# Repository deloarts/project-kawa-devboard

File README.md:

# Project Kawa Devboard

Documentation for the **Project Kawa Devboard**. This repository contains everything the Wifi-Client requires, including code, circuit design and housing.

> ⚠️ The Kawa Devboard is part of my condition monitoring project - Project Kawa - which isn't public. However, this repo is public, because the development board itself works pretty well after a long-term test of now over a year. You can use this board for your own project, if it fits your needs.
> 
> ✏️ The board is compatible with most open source home-automation systems, so feel free to use this board for other appliances than the Project Kawa.
>
> ✏️ In this repo you'll find not only the hardware of the devboard, but also the source. Keep in mind that the code is written for the Project Kawa Server, which isn't public, but feel free to tweak it for your own application.

## Table of contents

- [Project Kawa Devboard](#project-kawa-devboard)
  - [Table of contents](#table-of-contents)
  - [1 Description](#1-description)
  - [2 Usage](#2-usage)
    - [2.1 LED indicator](#21-led-indicator)
    - [2.2 Setup wifi](#22-setup-wifi)
    - [2.3 Reading sensor data](#23-reading-sensor-data)
    - [2.4 Status codes](#24-status-codes)
  - [3 Hardware](#3-hardware)
    - [3.1 Board](#31-board)
    - [3.2 Housing](#32-housing)
  - [4 Environment](#4-environment)
    - [4.1 Used software](#41-used-software)
    - [4.2 VS-Code setup](#42-vs-code-setup)
      - [4.2.1 code-workspace](#421-code-workspace)
      - [4.2.2 arduino.json](#422-arduinojson)
      - [4.2.3 c\_cpp\_properties.json](#423-c_cpp_propertiesjson)
    - [4.3 Eagle libraries](#43-eagle-libraries)
  - [5 Building \& Debugging](#5-building--debugging)
    - [5.1 Initial upload](#51-initial-upload)
    - [5.2 OTA upload](#52-ota-upload)
    - [5.3 Build the firmware](#53-build-the-firmware)
    - [5.4 Build the filesystem](#54-build-the-filesystem)
    - [5.5 Debug](#55-debug)
  - [6 License \& Disclaimer](#6-license--disclaimer)
  - [7 Changelog](#7-changelog)
    - [7.1 Firmware](#71-firmware)
    - [7.2 Filesystem](#72-filesystem)
    - [7.3 PCB](#73-pcb)
    - [7.4 Housing](#74-housing)
  - [8 To Do](#8-to-do)

## 1 Description

**Project Kawa Devboard** is part of the **Project Kawa** environment. This client is designed to test new sensors or new firmware, to debug code or find optimizations in the PCB layout. The latest version may not work without properly -> nightly builds.

This repository contains mostly code that is in development, as well as hardware-design that might only work under special conditions or differ from this documentation. This is not an out-of-the-box solution and requires some knowledge in a variety of fields. If you don't have an education in the field of electronics you should not proceed with this project, you might harm yourself or create damage by the risk of fire. Further you should be comfortable working with VS Code Workspaces.

Please note: All paths and settings are described for Windows. Will be updated in the future.

## 2 Usage

**This requires a working build of the firmware and filesystem already flashed to the chip, see [Initial Upload](#51-initial-upload)**. Please note: The description can differ from the actual process, depending on the development state of this device.

### 2.1 LED indicator

There are different kinds of LED-states to indicate the device's status:

- Short, almost unnoticeable blink: Wakeup from deepsleep, running normal cycle
- Rapid blinking 25 times: Wifi is not setup (this should happen after the initial upload)
- Rapid blinking 2 times: Changes have been written to the config
- On-Off every one second: Wifi-setup is running, hotspot is open

### 2.2 Setup wifi

The device needs to connect to your local network via 2.4GHz wifi. To setup your network's credentials you need to

- press and hold **BUTTON 1**
- click the **RESET** button
- the device opens a hotspot called **kawa setup**
- connect any wifi-enabled device to it
- enter your network-credentials
- select the connected sensor
- select the sleep interval (shorter intervals should only be used for testing and debugging)
- reset the controller afterwards

Now your *Kawa Devboard* is ready for use. As soon as the device connects to your wifi it will automatically connect to the server by its own, assuming that the server is running.

Note: The captive portal may not work properly, if so try:

- Use another device
- Click **yes** if your device asks you to stay connected (happens when the device notices, that no internet connection is available)
- Refresh the captive portal redirection page (sometimes the script or the stylesheet aren't loaded properly)
- Enter the IP address **1.2.3.4** manually into a browser

### 2.3 Reading sensor data

Once the wifi credentials are set up correct the device starts its main task: reading sensor data. There is no further interaction needed. The data is sent as json, example:

```json
{
  "device": {
    "id": "179309432879183923",
    "boardname": "devboard",
    "firmware_version": "0.1.0",
    "filesystem_version": "0.1.0",
    "mode": "production",
    "sensor_status": true,
    "sensor_name": "BMP280",
    "battery_status": true,
    "battery_value": 3.30,
    "sleep_interval": 3600,
    "connection_time": 7.334,
    "ssid": "the_network_ssid",
    "dbm": -78,
    "quality": 44,
    "hostname": "kawa_179309432879183923",
    "ip_address": "192.168.0.200",
    "mac_address": "00:80:41:ae:fd:7e"
  },
  "data": {
    "temperature": {
      "value": 25.2,
      "unit": "°C"
    },
    "pressure": {
      "value": 989.2,
      "unit": "mBar"
    },
    "altitude": {
      "value": 433,
      "unit": "m"
    },
    "humidity": {
      "value": 44.23,
      "unit": "%"
    }
  }
}
```

The server must answer with status code 201 and a json of the following format:

```json
value = {
    "status": "ok",
    "update_firmware": false,
    "new_firmware": "0.0.0",
    "update_spiffs": false,
    "new_spiffs": "0.0.0"
}
```

Due to the OTA-update functionality the client must know when to update. This is done by toggling the respective keys to **true**. With this the client will instantly download the given new version. The maximum size of the json is 2048 bytes.

### 2.4 Status codes

The devices accepts the following status codes as answer when posting data:

- **201**: data has been added to the database
- **406**: data has not been added to the database
- **500**: server error

## 3 Hardware

The core of this application is a ESP12F SOC by [espressif](https://www.espressif.com/en/products/socs/esp8266).

### 3.1 Board

The board is a two layered pcb, with mostly push-through components. This is due to easier hacking into the system, when something new needs testing without making a new pcb.

A complete bill of material can be found inside the [bom folder](docs/bom/).
For the production files select the latest zip-file inside the boards folder.

**Important note**: There is no deep discharge protection for the battery. Do not use non-protected batteries with this setup!

### 3.2 Housing

The housing is made with a 3D printer, files can be found inside the projects cad folder. More information will be added.

## 4 Environment

### 4.1 Used software

- The firmware is created with [VS Code](https://code.visualstudio.com/download) with the [Arduino-Core](https://www.arduino.cc/en/software) (extension: CTRL+P -> *ext install vscode-arduino*))
- The content of the filesystem is compiled with [mkspiffs](https://github.com/igrr/mkspiffs) and uploaded with [esptool](https://github.com/espressif/esptool).
- The pcb design is done with [Autodesk Eagle 9.6.2](https://www.autodesk.de/products/eagle/free-download), but may be continued with [EasyEDA](https://easyeda.com/) due to a better library-to-production support.

A full list of the used software, including versions, libraries and tools can be found at the top of the [src.ino](code/src/src.ino).

### 4.2 VS-Code setup

#### 4.2.1 code-workspace

Workspace-root is the repository-root. All relative paths are from this directory. Add the repository-root to a new workspace and save this workspace (can be saved inside or outside of the repo).

#### 4.2.2 arduino.json

Stored inside the **.vscode/** folder. This folder does not exist when cloning the repo and should appear automatically after creating the workspace, if not:

- Create it: [command-palette](https://code.visualstudio.com/docs/getstarted/userinterface#_command-palette) -> *Arduino: Initialize*
- Edit it: [command-palette](https://code.visualstudio.com/docs/getstarted/userinterface#_command-palette) -> *Arduino: Board Config*

Take the current board config from the description at the top of the [src file](code/src/src.ino).

Add the following lines to the json-file:

```json
  "sketch": "code\\src\\src.ino",
  "output": "code\\build\\firmware\\latest",
```

For the Arduino-Board-Config see the header-comment of the src-file.

#### 4.2.3 c_cpp_properties.json

Stored inside the **.vscode/** folder, create (or add):

```json
"configurations": [
    {
        "name": "Win32",
        "intelliSenseMode": "gcc-x64",
        "includePath": [
            "${workspaceRoot}\\code\\src\\",
            "${workspaceRoot}\\code\\src\\headers\\**",
            "C:\\Program Files (x86)\\Arduino\\hardware\\arduino\\avr\\cores\\arduino\\**",
            "${env:LOCALAPPDATA}\\Arduino15\\packages\\esp8266\\tools\\**",
            "${env:LOCALAPPDATA}\\Arduino15\\packages\\esp8266\\hardware\\esp8266\\3.0.0\\**",
            "${env:LOCALAPPDATA}\\Arduino15\\packages\\esp8266\\hardware\\esp8266\\3.0.0\\libraries\\**",
            "${env:HOMEPATH}\\Documents\\Arduino\\libraries\\ArduinoJson\\**",
            "${env:HOMEPATH}\\Documents\\Arduino\\libraries\\DallasTemperature\\**",
            "${env:HOMEPATH}\\Documents\\Arduino\\libraries\\OneWire\\**",
            "${env:HOMEPATH}\\Documents\\Arduino\\libraries\\Adafruit_Unified_Sensor\\**",
            "${workspaceRoot}\\code\\assets\\libraries\\Adafruit_BME280_Library\\**"
        ],
        "forcedInclude": [
            "C:\\Program Files (x86)\\Arduino\\hardware\\arduino\\avr\\cores\\arduino\\Arduino.h"
        ],
        "cStandard": "c11",
        "cppStandard": "c++17",
        "defines": []
    }
]
```

Please note: Some include-paths are only valid if you have chosen the standard path when you installed the Arduino-IDE on a Windows computer.

### 4.3 Eagle libraries

Can be found inside the pcb-folder. Must not be added to EAGLE if you don't plan on changing the board.

## 5 Building & Debugging

Tested and released firmware and filesystem versions can be found inside the respective folder

- [Firmware](code/build/firmware/)
- [Filesystem](code/build/filesystem/)

Those firmware-versions with the letter **d** after the version indicator are debug-versions. This means that you can hookup a serial-to-usb chip and get debug messages printed to a serial monitor. Baud-rate is always 115200. Versions without that letter are for production environment, you won't get any messages printed to the serial port.

### 5.1 Initial upload

To flash the firmware and filesystem initially you need to upload both with a usb-to-serial converter (popular method: use a [FTDI232 module](https://ftdichip.com/drivers/)). The upload process requires you to

- press and hold the **UPLOAD** button
- press and release the **RESET** button
- release the **UPLOAD** button as soon as the upload begins
- click the **RESET** button after the upload is done

The initial firmware can be uploaded with the command-palette -> *Arduino: Upload*.

The initial filesystem can be uploaded with *[SPIFFS for Arduino](https://github.com/esp8266/arduino-esp8266fs-plugin/releases)*.

### 5.2 OTA upload

New firmware/filesystem will be automatically installed by the **Project Kawa Server**. With every post-request (device -> server) the server answers with the newest firmware/filesystem version. If the current one is older the device will download and install the latest one. This process is called OTA.

This requires a working initial firmware to be flashed onto the device, see [Initial Setup](#51-initial-upload).

In order for the OTA to work you then have to copy the newest firmware/filesystem into the server's bin-directory. Please refer to the server's documentation for the correct filename or use the [test server](code/dev/test_server/test_server.py) from the **/dev** folder. The test server returns only the file set at the top-section. Do not use the test server in a production environment.

### 5.3 Build the firmware

The firmware is built when the src-file is compiled without any errors (command-palette -> *Arduino: Verify*). The binary file is then stored inside the latest-folder of build-directory, as instructed in the *4.2.2 arduino.json*.

### 5.4 Build the filesystem

Currently in testing.

### 5.5 Debug

To debug the firmware uncomment the **#define DEBUG** statement inside the [definitions.h](code/src/headers/definitions.h) file. Connect a serial-to-usb device to the RX-TX pins of the device, upload the changed code and open the serial monitor with 115200 baud rate.

To debug the captive portal content (files inside the [data folder](code/src/data/)) you can use any static file server. Tip: Run Python's builtin module **python -m http.server** inside the data folder.

## 6 License & Disclaimer

MIT.

All content on this repository is provided **as is**. None of these components have been tested or certified. The use of this content is **at your own risk**.

## 7 Changelog

### 7.1 Firmware

**v0.1.2**: Updated libraries.  
**v0.1.1**: Updated battery range.  
**v0.1.0**: Added location and updated api.  
**v0.0.0**: Creation.

### 7.2 Filesystem

**v0.1.0**: Added location.  
**v0.0.0**: Creation.

### 7.3 PCB

**Rev0**: Creation.

### 7.4 Housing

**Rev1**: Updated for FFF.  
**Rev0**: Creation.

## 8 To Do

- [ ] Fix: Wifi settings are overwritten when filesystem gets updated.
- [ ] Fix: Slow/laggy captive portal.
- [ ] Fix: Replace FS with LittleFS.
- [ ] Fix: Allow only one client at the captive portal.
- [ ] Replace: Change frontend to Vue CLI.
- [ ] Add: Switch sensor.
- [ ] Add: Air quality sensor.
- [ ] Add: Rain sensor (amount and state).
- [ ] Add: Moisture sensor.
- [ ] Add: Analog input (may require additional hardware).
- [ ] Test: Relay output (requires additional hardware).
- [ ] Test: LED controller (requires additional hardware).
- [ ] Test: Deep discharge protection (requires additional hardware).

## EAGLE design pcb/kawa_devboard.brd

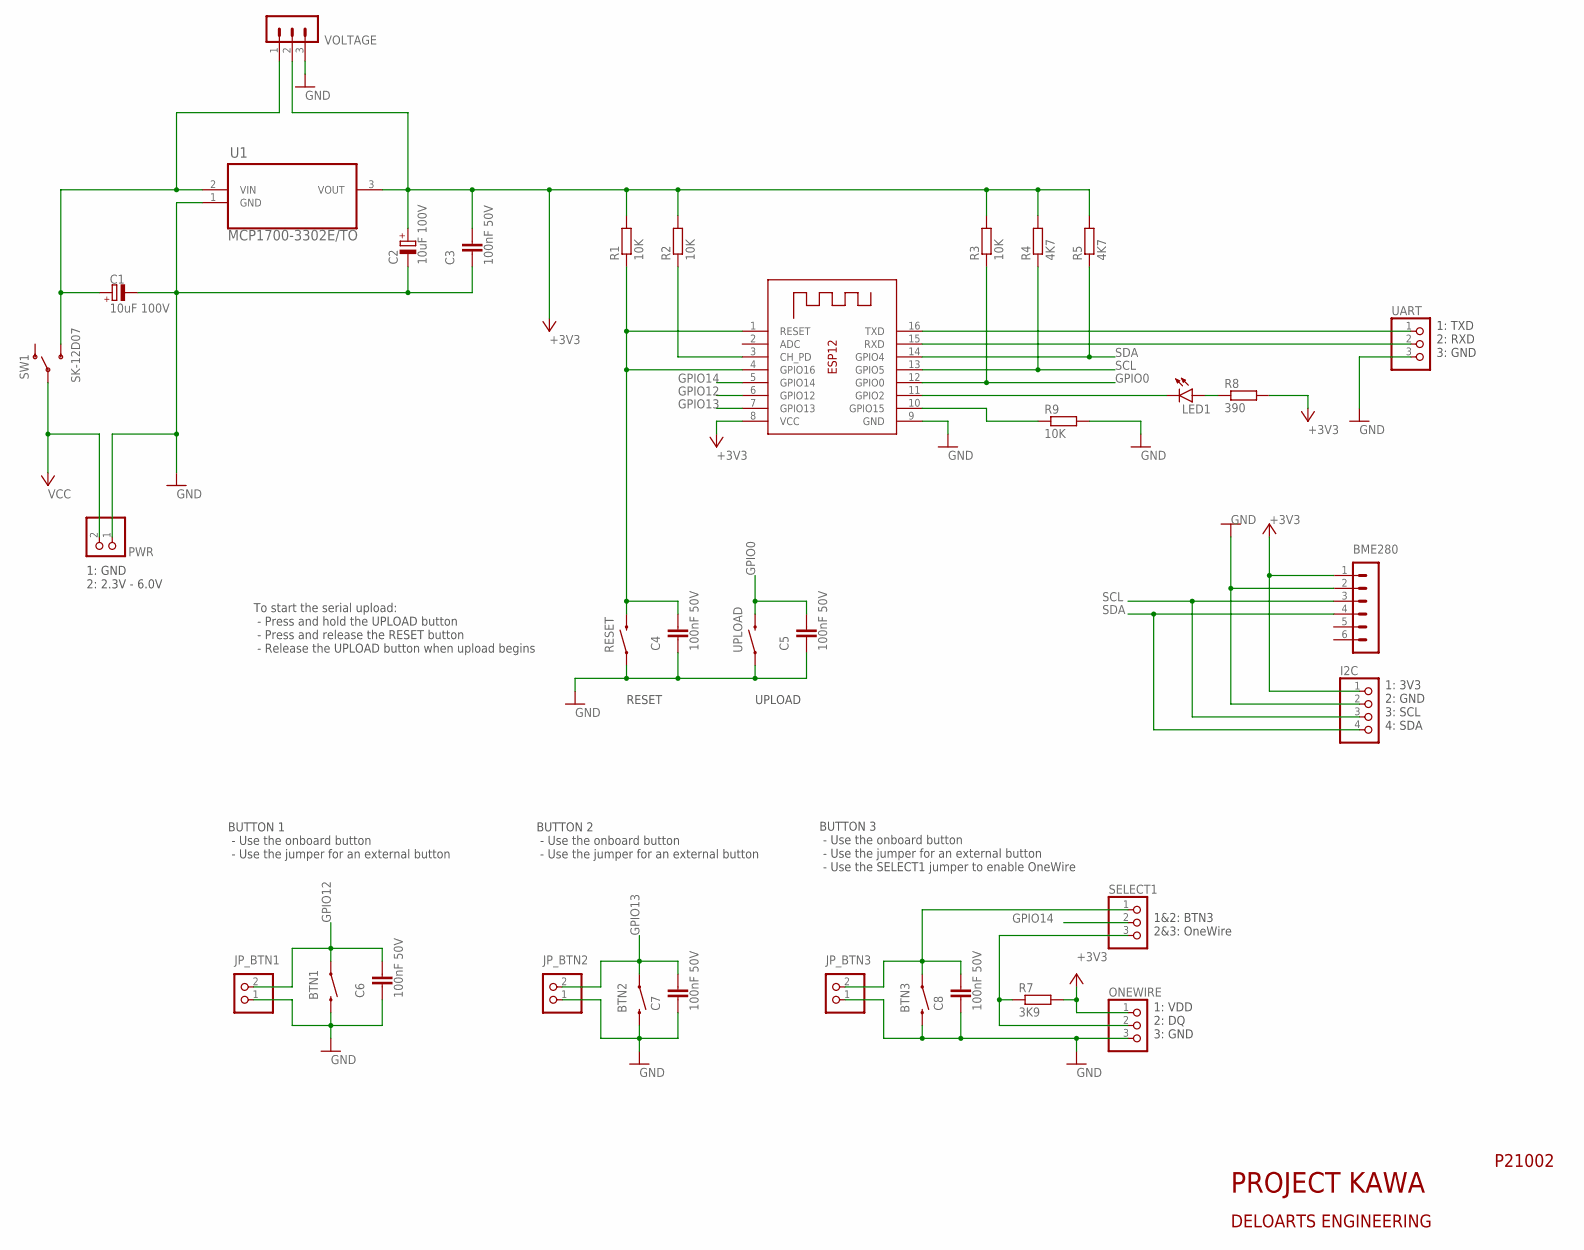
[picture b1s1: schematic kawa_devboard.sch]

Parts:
BME280: MA06-1
BTN1, BTN2, BTN3: MOMENTARY-SWITCH-SPST-PTH-6.0MM; TACTILE_SWITCH_PTH_6.0MM
C1, C2: 10uF 100V; E2-5
C3, C4, C5, C6, C7, C8: 100nF 50V; C2.5-3
I2C: PINHD-1X4; 1X04
JP_BTN1, JP_BTN2, JP_BTN3: PINHD-1X2/90; 1X02/90
LED1: LEDSFH480; SFH480
ONEWIRE: PINHD-1X3/90; 1X03/90
PWR: PINHD-1X2/90; 1X02/90
R1, R2, R3, R9: 10K; 0204/7
R4, R5: 4K7; 0204/7
R7: 3K9; 0204/7
R8: 390; 0204/7
RESET: MOMENTARY-SWITCH-SPST-PTH-6.0MM; TACTILE_SWITCH_PTH_6.0MM
SELECT1: PINHD-1X3; 1X03
SW1: SK-12D07; SK12SWITCH
U1: MCP1700-3302E/TO; TO127P254X495-3
UART: PINHD-1X3; 1X03
UPLOAD: MOMENTARY-SWITCH-SPST-PTH-6.0MM; TACTILE_SWITCH_PTH_6.0MM
VOLTAGE: MA03-1
X1: ESP-12

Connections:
+3V3: BME280.1, C2.+, C3.1, I2C.1, ONEWIRE.1, R1.2, R2.2, R3.2, R4.2, R5.2, R7.2, R8.2, U1.3 (VOUT), VOLTAGE.2, X1.8 (VCC)
BTN3: BTN3.1, C8.1, JP_BTN3.2, SELECT1.1
CH_PD: R2.1, X1.3 (CH_PD)
DQ: ONEWIRE.2, R7.1, SELECT1.3
GND: BME280.2, BTN1.3 (2), BTN2.3 (2), BTN3.3 (2), C1.-, C2.-, C3.2, C4.2, C5.2, C6.2, C7.2, C8.2, I2C.2, JP_BTN1.1, JP_BTN2.1, JP_BTN3.1, ONEWIRE.3, PWR.1, R9.2, RESET.1, U1.1 (GND), UART.3, UPLOAD.1, VOLTAGE.3, X1.9 (GND)
GPIO0: C5.1, R3.1, UPLOAD.3 (2), X1.12 (GPIO0)
GPIO2: LED1.K (C), X1.11 (GPIO2)
GPIO12: BTN1.1, C6.1, JP_BTN1.2, X1.6 (GPIO12)
GPIO13: BTN2.1, C7.1, JP_BTN2.2, X1.7 (GPIO13)
GPIO14: SELECT1.2, X1.5 (GPIO14)
GPIO15: R9.1, X1.10 (GPIO15)
LED1: LED1.A, R8.1
RST: C4.1, R1.1, RESET.3 (2), X1.1 (RESET), X1.4 (GPIO16)
RXD: UART.2, X1.15 (RXD)
SCL: BME280.3, I2C.3, R4.1, X1.13 (GPIO5)
SDA: BME280.4, I2C.4, R5.1, X1.14 (GPIO4)
TXD: UART.1, X1.16 (TXD)
VCC: PWR.2, SW1.P2
VIN: C1.+, SW1.IN (S), U1.2 (VIN), VOLTAGE.1

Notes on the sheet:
1: TXD 2: RXD 3: GND
RESET
UPLOAD
BUTTON 1 - Use the onboard button - Use the jumper for an external button
BUTTON 2 - Use the onboard button - Use the jumper for an external button
BUTTON 3 - Use the onboard button - Use the jumper for an external button - Use the SELECT1 jumper to enable OneWire
1: 3V3 2: GND 3: SCL 4: SDA
1: GND 2: 2.3V - 6.0V
1: VDD 2: DQ 3: GND
1&2: BTN3 2&3: OneWire
To start the serial upload: - Press and hold the UPLOAD button - Press and release the RESET button - Release the UPLOAD button when upload begins
P21002
PROJECT KAWA
DELOARTS ENGINEERING

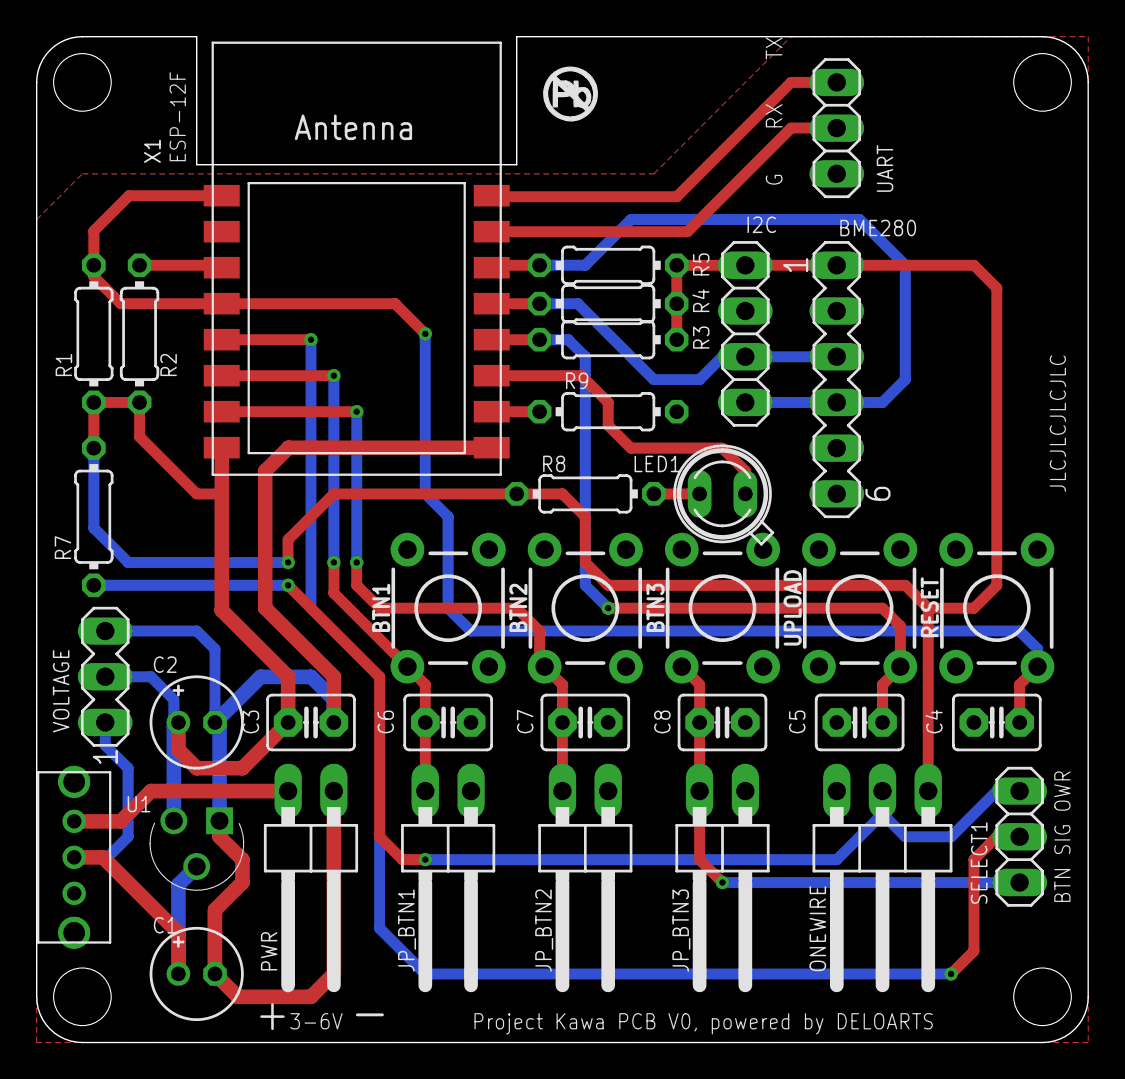
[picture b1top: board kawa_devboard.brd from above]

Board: 2 copper layers, 58.4 x 55.9 mm, 36 parts (0 on the bottom side), 19 nets.

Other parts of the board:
U$1: NO_PB_LOGO_0.120

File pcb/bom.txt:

Qty Value                           Device                          Package                  Parts                           Description                          
1                                   ESP-12                          ESP-12                   X1                                                                   
1                                   LEDSFH480                       SFH480                   LED1                            LED                                  
1                                   MA03-1                          MA03-1                   VOLTAGE                         PIN HEADER                           
1                                   MA06-1                          MA06-1                   BME280                          PIN HEADER                           
4                                   PINHD-1X2/90                    1X02/90                  JP_BTN1, JP_BTN2, JP_BTN3, PWR  PIN HEADER                           
2                                   PINHD-1X3                       1X03                     SELECT1, UART                   PIN HEADER                           
1                                   PINHD-1X3/90                    1X03/90                  ONEWIRE                         PIN HEADER                           
1                                   PINHD-1X4                       1X04                     I2C                             PIN HEADER                           
6   100nF 50V                       C2,5-3                          C2.5-3                   C3, C4, C5, C6, C7, C8          CAPACITOR                            
4   10K                             R-EU_0204/7                     0204/7                   R1, R2, R3, R9                  RESISTOR, European symbol            
2   10uF 100V                       CPOL-EUE2-5                     E2-5                     C1, C2                          POLARIZED CAPACITOR, European symbol 
1   390                             R-EU_0204/7                     0204/7                   R8                              RESISTOR, European symbol            
1   3K9                             R-EU_0204/7                     0204/7                   R7                              RESISTOR, European symbol            
2   4K7                             R-EU_0204/7                     0204/7                   R4, R5                          RESISTOR, European symbol            
1   MCP1700-3302E/TO                MCP1700-3302E/TO                TO127P254X495-3          U1                              IC LDO REG 250MA 5.0V Check prices   
5   MOMENTARY-SWITCH-SPST-PTH-6.0MM MOMENTARY-SWITCH-SPST-PTH-6.0MM TACTILE_SWITCH_PTH_6.0MM BTN1, BTN2, BTN3, RESET, UPLOAD Momentary Switch (Pushbutton) - SPST 
1   SK-12D07                        SK-12D07                        SK12SWITCH               SW1

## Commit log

2021-07-12 added cad files
2021-07-16 added todo
2021-07-16 added extension info
2021-07-16 updated firmware information
2021-07-17 added fix
2021-07-23 added note for debug-versions
2021-07-23 added json format to readme
2021-07-30 updated ota info
2021-09-10 updated test server response status code
2021-09-10 added location as device parameter
2021-09-10 updated requests to match the server's API
2021-09-10 increased firmware and filesystem version
2021-09-10 renamed firmware to match the server
2021-09-10 added new firmware release
2021-09-10 renamed filesystem file to match the server
2021-09-10 released new filesystem binary
2021-09-11 added bill of material and pdf schematics
2021-09-14 added datasheets
2021-09-14 updated battery range
2021-11-21 updated housing
2021-11-28 updated libraries
2021-11-28 added debug version of 0.1.2
2023-08-27 Public Repo

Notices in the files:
parts and their libraries:
SparkFun-Switches: Licensing: Creative Commons ShareAlike 4.0 International - https://creativecommons.org/licenses/by-sa/4.0
